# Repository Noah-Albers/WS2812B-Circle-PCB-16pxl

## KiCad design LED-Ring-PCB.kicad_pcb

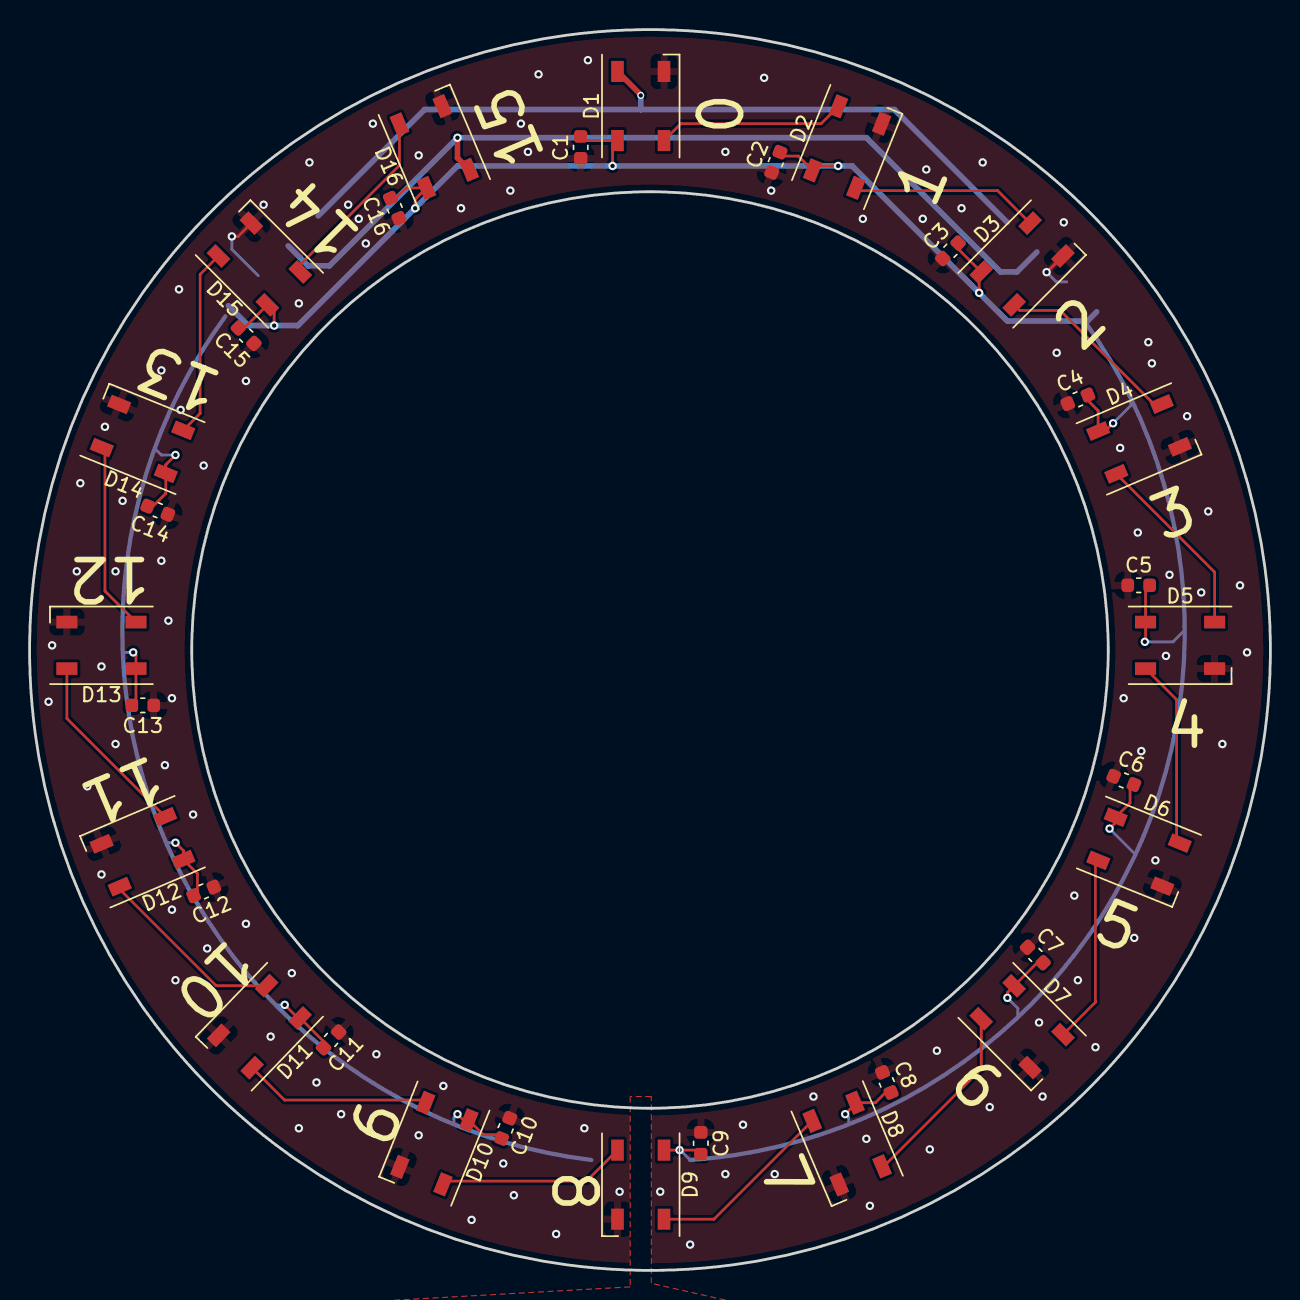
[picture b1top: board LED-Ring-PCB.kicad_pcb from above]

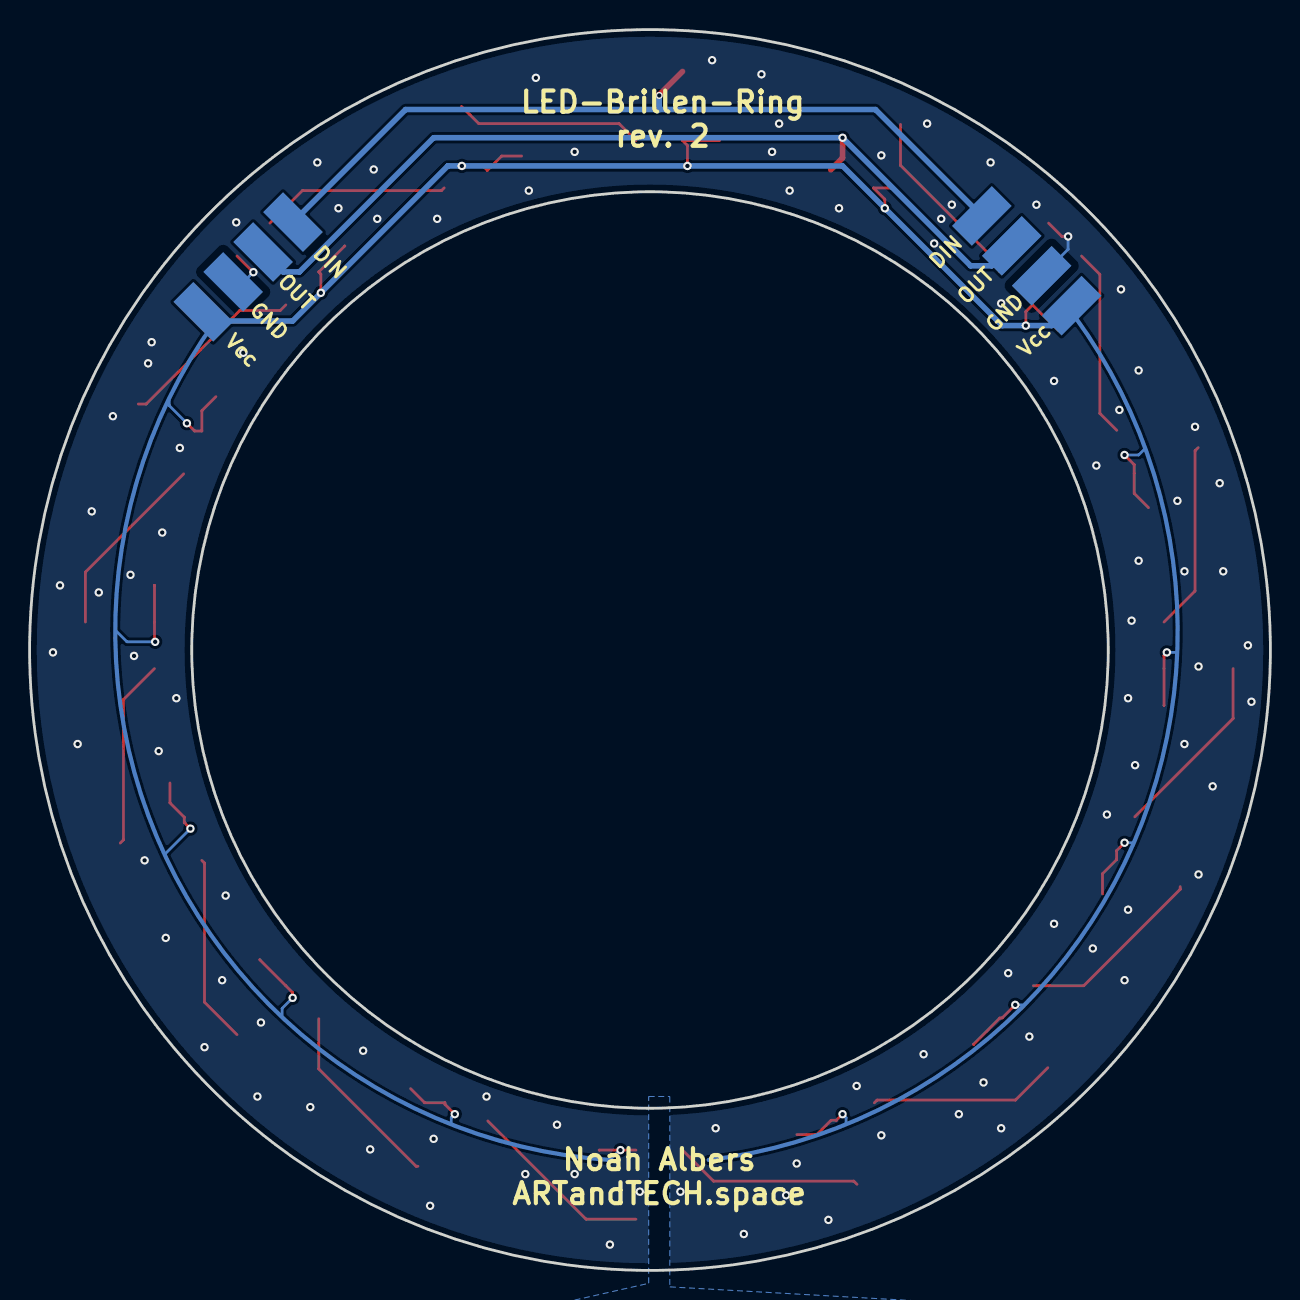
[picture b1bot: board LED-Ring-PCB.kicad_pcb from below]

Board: 2 copper layers, 88.0 x 88.0 mm, 34 parts (2 on the bottom side), 19 nets.

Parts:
C1, C2, C3, C4, C5, C6, C7, C8, C9, C10, C11, C12, C13, C14, C15, C16: C; C_0603_1608Metric
D1, D2, D3, D4, D5, D6, D7, D8, D9, D10, D11, D12, D13, D14, D15, D16: WS2812B; LED_WS2812B_PLCC4_5.0x5.0mm_P3.2mm
J1, J2: Conn_01x04; 01x04_SMD_Pads

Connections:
/DIN: D1.4 (DIN), J1.1, J2.1
/DOUT: D16.2 (DOUT), J1.2, J2.2
GND: C1.1, C2.1, C3.1, C4.1, C5.1, C6.1, C7.1, C8.1, C9.1, C10.1, C11.1, C12.1, C13.1, C14.1, C15.1, C16.1, D1.3 (VSS), D2.3 (VSS), D3.3 (VSS), D4.3 (VSS), D5.3 (VSS), D6.3 (VSS), D7.3 (VSS), D8.3 (VSS), D9.3 (VSS), D10.3 (VSS), D11.3 (VSS), D12.3 (VSS), D13.3 (VSS), D14.3 (VSS), D15.3 (VSS), D16.3 (VSS), J1.3, J2.3
unnamed: D1.2 (DOUT), D2.4 (DIN)
unnamed: D2.2 (DOUT), D3.4 (DIN)
unnamed: D3.2 (DOUT), D4.4 (DIN)
unnamed: D4.2 (DOUT), D5.4 (DIN)
unnamed: D5.2 (DOUT), D6.4 (DIN)
unnamed: D6.2 (DOUT), D7.4 (DIN)
unnamed: D7.2 (DOUT), D8.4 (DIN)
unnamed: D8.2 (DOUT), D9.4 (DIN)
unnamed: D9.2 (DOUT), D10.4 (DIN)
unnamed: D10.2 (DOUT), D11.4 (DIN)
unnamed: D11.2 (DOUT), D12.4 (DIN)
unnamed: D12.2 (DOUT), D13.4 (DIN)
unnamed: D13.2 (DOUT), D14.4 (DIN)
unnamed: D14.2 (DOUT), D15.4 (DIN)
unnamed: D15.2 (DOUT), D16.4 (DIN)
VCC: C1.2, C2.2, C3.2, C4.2, C5.2, C6.2, C7.2, C8.2, C9.2, C10.2, C11.2, C12.2, C13.2, C14.2, C15.2, C16.2, D1.1 (VDD), D2.1 (VDD), D3.1 (VDD), D4.1 (VDD), D5.1 (VDD), D6.1 (VDD), D7.1 (VDD), D8.1 (VDD), D9.1 (VDD), D10.1 (VDD), D11.1 (VDD), D12.1 (VDD), D13.1 (VDD), D14.1 (VDD), D15.1 (VDD), D16.1 (VDD), J1.4, J2.4

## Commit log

2024-11-02 Added rev. 1
2024-11-02 Updated capacitor-packages from 0402 to 0603
2024-11-03 Added Pritings for the numbers. (Rev. 2)
